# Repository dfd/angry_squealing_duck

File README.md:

# Angry Squealing Duck

A guitar pedal: a thick octave-fuzz feeding a dynamics-driven envelope band-pass
("Q-Tron") filter. Designed and voiced entirely in **ngspice**, validated against
real-part models, ready for KiCad.

**Controls (4 knobs + 2 footswitches):**
- **Volume** — output level
- **Anger** — fuzz amount / sustain (Big-Muff-style)
- **Squeal** — up-octave level: CCW = none, ~noon = "ring on top", CW = octave-dominant blast
- **Quack** — envelope band-pass intensity (ganged sweep depth + resonance Q)
- **Master** true-bypass footswitch, and a dedicated **Squeal (octave) footswitch**
  (kick the octave in/out, Hoof-Reaper style)

All knobs CCW = that effect off.

## Signal architecture

```
 IN ─► Input buffer ─► SPLIT ─┬─ AUDIO: Fuzz(Anger) ─┬─► BP envelope filter(Quack) ──┐
                              │                       └─► Octave-up(Squeal) ─► fixed HP┤─►[Volume]─► OUT
                              └─ CONTROL: Envelope follower (raw) ─► Iabc (cutoff) ─────┘
```

Key voicing decisions (each one earned the hard way — see `git log` / memory):
- **Octave AFTER the fuzz** (Octavia / Fender-Blender pattern): rectifying the distorted
  signal yields a prominent ring. Octave *before* the fuzz buried it ~30 dB under the
  fuzz's odd harmonics.
- **Body and octave on separate filter paths** ("hybrid" route): the fuzz body goes
  through the **band-pass** envelope filter (it quacks); the octave goes through a
  **fixed high-pass** (stays clear/bright instead of being swept under). A single shared
  filter ("mixed") muffled the octave.
- **Envelope tapped from the RAW split** (pre-fuzz) so the filter tracks picking dynamics
  — fuzz compresses dynamics away.

## Design choices

- Single **9 V** supply, **op-amp-buffered 4.5 V** virtual ground (`vref`) — a passive
  divider sags under the high-gain fuzz. Every stage input is AC-coupled.
- **Fuzz** = 3-stage cascaded **Big-Muff-style soft-clipper** with asymmetric stages for
  warmth (`fuzz_muff.cir`, default). A single-stage hard clipper (`fuzz.cir`, DOD-250
  family) is kept selectable via the `muff` param.
- **Octave** = op-amp **precision full-wave rectifier** (`fwr.cir`), no transformer.
  `octave_gen.cir` produces octave-only; Squeal level is **quadratic** so noon = ring,
  full = blast (`goct=8`, ~+9 dB octave-over-body, calibrated on real DI clips).
- **Envelope follower** = precision rectifier + **2-pole averaging** (not peak-detect,
  which hunted in a ~12 Hz limit cycle that re-triggered the filter on held notes).
- **Filter** = **LM13700 OTA state-variable** filter (`vcf.cir` behavioral / `vcf_real.cir`
  real). Has LP/BP/HP/mixed taps (Q-Tron-style mode); the hybrid route uses BP for the
  body. Quack maps to a **linear Q (0.7→3.5)** and an envelope-swept cutoff (gm = Iabc).
  gm control is ground-referenced to avoid a virtual-ground latch.
- **Behavioral-ideal first** to lock topology/voicing, then **real part models** for build
  accuracy (`opamp_real.sub` = TL072, `lm13700.sub` = OTA) — validated: voicing essentially
  unchanged on real silicon. See `memory` / `real-parts-and-build-notes`.

## Status

Design, voicing, real-part validation, **and a routed KiCad PCB are complete.**

| done | |
|---|---|
| ✅ | All blocks designed + integrated (input buffer → fuzz → octave → filter → volume) |
| ✅ | Voiced by ear on real guitar (MOTU M2), grid of Squeal×Anger×Quack rendered |
| ✅ | Real part models (TL072 + LM13700) — chain converges, voicing holds |
| ✅ | All-real buildable netlist (`pedal_build.cir`, no B-sources) — re-validated |
| ✅ | Quack sweep restored: V-to-I gain ×73 → body cutoff ~280 Hz→2.1 kHz, auditioned-good |
| ✅ | KiCad PCB: placed, auto-routed, gerbers exported |
| ✅ | **Tier-1 de-risk audit** (`kicad/AUDIT.md`): caught + fixed **10 reversed diodes**; added per-IC decoupling + Schottky protection + center-neg polarity; **DRC 0 unconnected / 0 violations** |

**Quack note:** the real envelope is tiny (~0.04 V peak), so the V-to-I needs high gain
(`Rdi`/`Rdj` = 1.5k, `Rdf`/`Rdk` = 110k → ×73) for the filter to sweep. Quack is most
audible at lower Squeal — at full Squeal the octave sits on top by design.

**Audit caught a board-killer:** `duck.py` (hand-translated) had 10/14 diodes reversed
(fuzz clippers + both rectifiers) — ERC + sim pass anyway since the SPICE is a separate,
correct source. Fixed to match SPICE; see `kicad/AUDIT.md`. **Not yet hardware-validated:**
real noise floor + the LM13700 filter's behavior (the `/50` attenuation hack, Iabc ceiling) —
confirm by breadboarding the filter + fuzz before fab (`kicad/breadboard/`).

## Layout

- `spice/lib/`    — models: `opamp.sub` (ideal), `opamp_real.sub` (TL072),
  `lm13700.sub` (OTA), `diode.mod` (1N4148), `supply.cir` (buffered vref)
- `spice/blocks/` — one `.subckt` per block: `input_buffer`, `fuzz`, `fuzz_muff`, `fwr`,
  `octave_rect`/`octave_gen`, `hpf`, `gmint`+`vcf`/`vcf_real`, `envfollow`,
  `duck`(mixed)/`duck_split`(hybrid/parallel), `pedal`
- `spice/tests/`  — per-block test benches
- `sim/`          — Python harness: `run.py`, `render.py`, `octave_balance.py`,
  `fft_report.py`, `spicelib.py`, `extract_sample.py`
- `audio/in/`     — committed DI samples; `audio/out/` — rendered WAVs (git-ignored)
- `raw_wavs/`     — large source recordings (git-ignored)
- `kicad/`        — the board, generated programmatically:
  - `duck.py` (SKiDL netlist generator) → `duck.net` (ERC-clean) + `BOM.md`
  - `build_pcb.py` (pcbnew: parse netlist → place → board) ; `finish_pcb.py` (values + GND pour)
  - `duck.kicad_pcb` (routed, DRC-clean) ; `gerbers/` + `duck.drl` + `duck-pos.csv` (fab-ready)
  - `duck_3d_top.png` / `duck_3d_persp.png` (3D renders; or open the `.kicad_pcb` in pcbnew → `Alt+3`)
  - `AUDIT.md` (netlist-translation audit + gap fixes) ; `BOM.md` ; `COST.md` (build-cost estimate)
  - `pedal_build.cir` in `spice/blocks/` is the all-real buildable schematic-of-record
- `kicad/breadboard/` — prototype-first docs (build it on a breadboard before the PCB):
  - `BUILD_GUIDE.md` (staged bring-up) + `CONNECTIONS.md` (per-stage wiring tables, net = row)
  - `gen_blocks.py` / `make_tables.py` (generators) ; `0*.png` drawn schematics (simple stages)
- `audio/out/build_grid/` + `build_grid_orig/` — full real-parts grids (Squeal×Anger×Quack ∈ {0,0.5,1})

## KiCad / PCB workflow

The board is generated entirely by script (no GUI), bridging two Pythons because
`pcbnew` is built for system Python 3.14 while the sim harness uses uv's 3.13:
```
# 1. netlist (uv / 3.13)
KICAD8_SYMBOL_DIR=/usr/share/kicad/symbols uv run kicad/duck.py     # -> duck.net (+ ERC)
# 2. place + board (system python 3.14, needs pcbnew)
/usr/bin/python3 kicad/build_pcb.py                                 # -> duck.kicad_pcb
# 3. route: export DSN, run freerouting (needs a display, e.g. :0), import SES
/usr/bin/python3 -c "import pcbnew,sys; b=pcbnew.LoadBoard('kicad/duck.kicad_pcb'); pcbnew.ExportSpecctraDSN(b,'/tmp/duck.dsn')"
DISPLAY=:0 java -jar freerouting.jar -de /tmp/duck.dsn -do /tmp/duck.ses -mp 14
/usr/bin/python3 -c "import pcbnew; b=pcbnew.LoadBoard('kicad/duck.kicad_pcb'); pcbnew.ImportSpecctraSES(b,'/tmp/duck.ses'); pcbnew.SaveBoard('kicad/duck.kicad_pcb',b)"
# 4. finishing pass (snap values + GND pour) + checks + fab outputs
/usr/bin/python3 kicad/finish_pcb.py
kicad-cli pcb drc kicad/duck.kicad_pcb
kicad-cli pcb export gerbers --output kicad/gerbers/ kicad/duck.kicad_pcb
```
Board: 2-layer, 175×120 mm (1590DD-class), 6× TL074 + 1× LM13700 + 14× 1N4148,
4 knobs (Volume / Anger / Squeal / Quack-dual-gang). No graphical schematic
(eeschema has no scripting API) — `pedal_build.cir` + `duck.py` are the design-of-record.

## Prototype it first (breadboard)

`kicad/breadboard/` holds **prototype-first** docs. Build + test the circuit on solderless
breadboards one stage at a time before committing to the PCB — see `BUILD_GUIDE.md` for the
staged bring-up order (supply → input → fuzz → octave → envelope → V-to-I → filter → output)
and `CONNECTIONS.md` for per-stage wiring tables (**each net = one breadboard row**; IC pins
annotated). Each stage uses its own op-amp IC (not the PCB's shared packing) so it tests
standalone. Regenerate with `gen_blocks.py` + `make_tables.py`. (SKiDL's schematic auto-router
only handles the simple stages, so the dense ones are table-only — better for breadboarding anyway.)

## Workflow

Run a block test bench:
```
uv run sim/run.py spice/tests/tb_input_buffer.cir
```
Render guitar through the pedal (→ `audio/out/`):
```
# the LOCKED, buildable design (= the PCB): real parts, no B-sources, V-to-I gain x73
uv run sim/render.py [wav] --build --squeal 1 --anger 0.8 --quack 0.6 [--subdir name]
# the behavioral routes (faster iteration / experiments):
uv run sim/render.py [wav] --route hybrid --squeal 1 --anger 0.8 --quack 0.6 [--real]
```
- **`--build`** = `pedal_build.cir`, the all-real buildable pedal that matches the PCB (use this).
- `--real` = TL072 + LM13700 models on the behavioral chain · `--route` = mixed|hybrid|parallel
- Scratch files are unique per render, so render a grid in parallel on many cores:
  `... | xargs -P 24 -I A sh -c 'uv run sim/render.py A'`
  (the committed `audio/out/build_grid/` + `build_grid_orig/` are the `--build` grids of
  Squeal×Anger×Quack ∈ {0, 0.5, 1.0} on both DI samples).

Measure octave-vs-body level on real clips (don't trust single-note benches — they
over-read the octave ~6 dB):
```
uv run sim/octave_balance.py --wav audio/in/di_sample.wav --squeal 1.0 --goct 8
```

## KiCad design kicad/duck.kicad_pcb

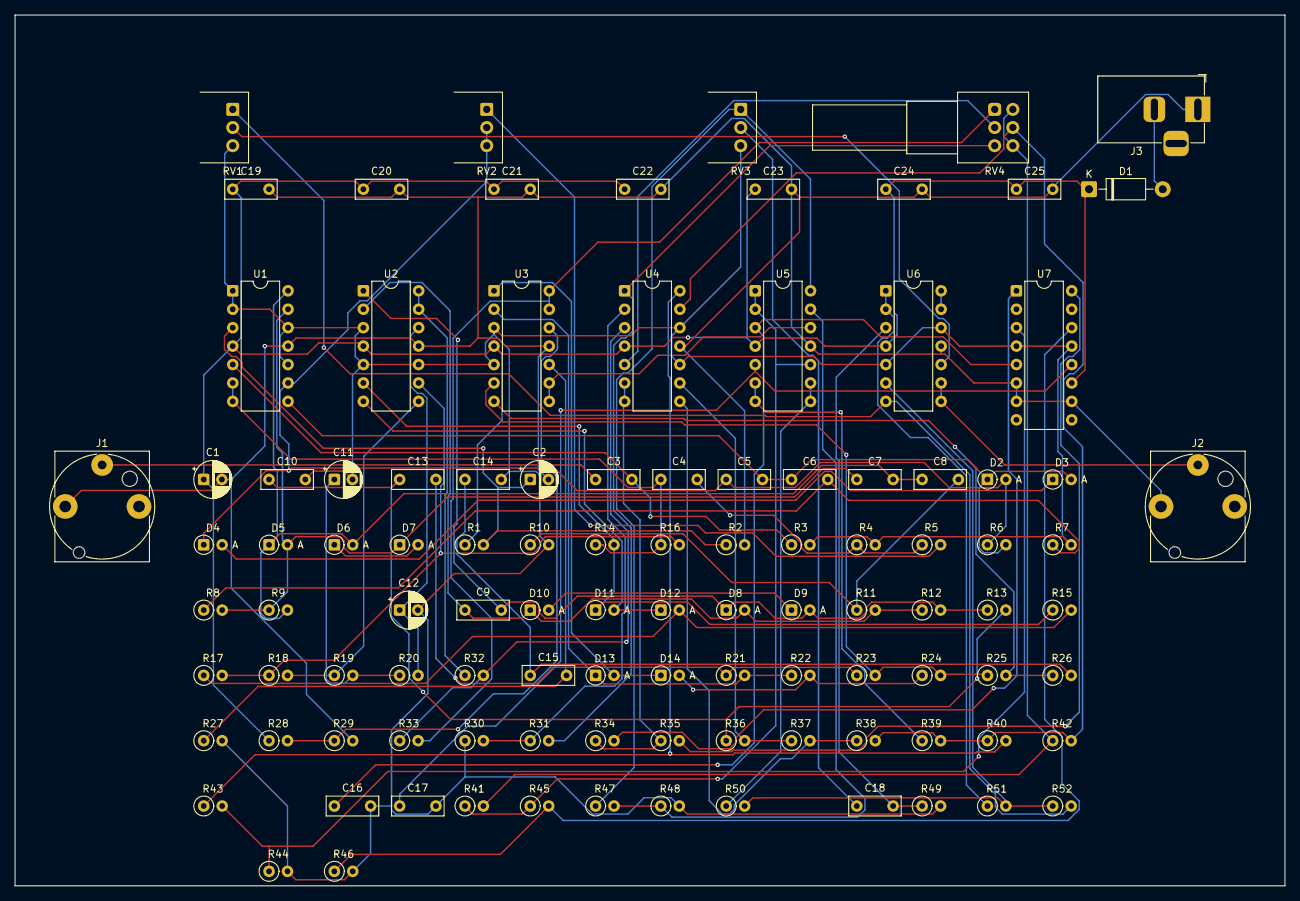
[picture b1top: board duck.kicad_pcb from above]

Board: 2 copper layers, 175.0 x 120.0 mm, 105 parts (0 on the bottom side), 70 nets.

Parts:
C1: 100u; CP_Radial_D5.0mm_P2.50mm
C2: 47u; CP_Radial_D5.0mm_P2.50mm
C3, C4, C6, C8, C19, C20, C21, C22, C23, C24, C25: 100n; C_Rect_L7.0mm_W2.5mm_P5.00mm
C5, C7, C9: 1.5n; C_Rect_L7.0mm_W2.5mm_P5.00mm
C10: 27n; C_Rect_L7.0mm_W2.5mm_P5.00mm
C11, C12: 220n; CP_Radial_D5.0mm_P2.50mm
C13: 47n; C_Rect_L7.0mm_W2.5mm_P5.00mm
C14: 12n; C_Rect_L7.0mm_W2.5mm_P5.00mm
C15: 1u; C_Rect_L7.0mm_W2.5mm_P5.00mm
C16, C17: 10n; C_Rect_L7.0mm_W2.5mm_P5.00mm
C18: 22n; C_Rect_L7.0mm_W2.5mm_P5.00mm
D1: 1N5817; D_DO-41_SOD81_P10.16mm_Horizontal
D2, D3, D4, D5, D6, D7, D8, D9, D10, D11, D12, D13, D14: 1N4148; D_DO-35_SOD27_P2.54mm_Vertical_AnodeUp
J1, J2: AudioJack2; Jack_6.35mm_Neutrik_NJ3FD-V_Vertical
J3: Barrel_Jack; BarrelJack_Horizontal
R1, R2, R6, R9, R27, R28: 100k; R_Axial_DIN0207_L6.3mm_D2.5mm_P2.54mm_Vertical
R3, R4, R7, R10: 1M; R_Axial_DIN0207_L6.3mm_D2.5mm_P2.54mm_Vertical
R5, R13: 2.2k; R_Axial_DIN0207_L6.3mm_D2.5mm_P2.54mm_Vertical
R8, R11: 12k; R_Axial_DIN0207_L6.3mm_D2.5mm_P2.54mm_Vertical
R12, R47: 68k; R_Axial_DIN0207_L6.3mm_D2.5mm_P2.54mm_Vertical
R14, R15, R16, R18, R21, R22, R23, R25, R34, R35, R36, R37, R38, R39, R40, R48: 10k; R_Axial_DIN0207_L6.3mm_D2.5mm_P2.54mm_Vertical
R17, R24: 4.7k; R_Axial_DIN0207_L6.3mm_D2.5mm_P2.54mm_Vertical
R19, R20: 15k; R_Axial_DIN0207_L6.3mm_D2.5mm_P2.54mm_Vertical
R26: 3.3k; R_Axial_DIN0207_L6.3mm_D2.5mm_P2.54mm_Vertical
R29, R49, R50, R51, R52: 22k; R_Axial_DIN0207_L6.3mm_D2.5mm_P2.54mm_Vertical
R30, R32: 1.5k; R_Axial_DIN0207_L6.3mm_D2.5mm_P2.54mm_Vertical
R31, R33: 110k; R_Axial_DIN0207_L6.3mm_D2.5mm_P2.54mm_Vertical
R41: 6.8k; R_Axial_DIN0207_L6.3mm_D2.5mm_P2.54mm_Vertical
R42: 39k; R_Axial_DIN0207_L6.3mm_D2.5mm_P2.54mm_Vertical
R43, R45: 47k; R_Axial_DIN0207_L6.3mm_D2.5mm_P2.54mm_Vertical
R44, R46: 1k; R_Axial_DIN0207_L6.3mm_D2.5mm_P2.54mm_Vertical
RV1, RV2, RV3: 100k; Potentiometer_Alps_RK097_Single_Horizontal
RV4: 100k; Potentiometer_Alps_RK097_Dual_Horizontal
U1, U2, U3, U4, U5, U6: TL074; DIP-14_W7.62mm
U7: LM13700; DIP-16_W7.62mm

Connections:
BODYF: R50.1, U5.8, U5.9
BP: R41.1, R45.1, U5.1, U5.2, U5.10
CV: R32.1, U2.13, U2.14
ECTL: R31.2, RV4.3, U4.1
FZ: C10.1, C13.1, R13.2, R36.1
FZ1: C5.2, C6.1, D2.1, D3.2, R6.2, U1.8
FZ2: C7.2, C8.1, D5.1, D6.2, R9.2, U1.14
FZ3: C9.2, D8.1, D9.2, R12.2, R13.1, U2.1
GND: C1.2, C2.2, C19.2, C20.2, C21.2, C22.2, C23.2, C24.2, C25.2, J1.S, J2.S, J3.1, R2.2, R29.2, U1.11, U2.11, U3.11, U4.11, U5.11, U6.11, U7.6, U7.7, U7.10
HP: R40.2, R43.1, U4.14
LP: R39.1, U5.6, U5.7
unnamed: C4.2, R4.1, R5.1
unnamed: R5.2, RV2.1
unnamed: C5.1, D2.2, D4.1, R6.1, RV2.2, RV2.3, U1.9
unnamed: D3.1, D4.2
unnamed: C6.2, R7.1, R8.1
unnamed: C7.1, D5.2, D7.1, R8.2, R9.1, U1.13
unnamed: D6.1, D7.2
unnamed: C8.2, R10.1, R11.1
unnamed: C9.1, D8.2, D10.1, R11.2, R12.1, U2.2
unnamed: D9.1, D10.2
unnamed: D11.1, R14.2, R15.1, U2.6
unnamed: R16.2, R17.2, R18.1, U2.9
unnamed: D12.2, R15.2, R17.1
unnamed: D11.2, D12.1, U2.7
unnamed: C11.1, R19.2, R20.1
unnamed: C12.1, R20.2, U2.12
unnamed: C13.2, R21.1, R23.1
unnamed: R25.2, R26.1, U3.7
unnamed: D13.1, R21.2, R22.1, U3.2
unnamed: R23.2, R24.2, R25.1, U3.6
unnamed: D14.2, R22.2, R24.1
unnamed: D13.2, D14.1, U3.1
unnamed: C14.1, C15.1, R26.2
unnamed: C15.2, R27.1, U3.10
unnamed: R28.2, R29.1, U3.12
unnamed: R30.2, R31.1, U4.2
unnamed: R32.2, R33.1, U4.3
unnamed: R34.2, U7.1
unnamed: R35.2, U7.16
unnamed: R37.2, R38.1, U4.8
unnamed: R36.2, R37.1, U4.9
unnamed: R38.2, R39.2, R40.1, R42.2, RV4.5, U4.13
unnamed: R41.2, R42.1, RV4.4, RV4.6
unnamed: R43.2, R44.1, U7.3
unnamed: C16.1, U5.3, U7.5
unnamed: R45.2, R46.1, U7.14
unnamed: C17.1, U5.5, U7.12
unnamed: R47.1, RV3.1, U5.14
unnamed: R47.2, R48.1, U5.13
unnamed: C18.1, RV3.2
unnamed: C18.2, R49.1, U6.3
unnamed: R50.2, R51.2, R52.1, U6.6
unnamed: RV1.2, U6.10
unnamed: U6.13, U6.14
NP: C3.2, R3.1, U1.5
NREF: C2.1, R1.2, R2.1, U1.3
OCTF: R51.1, U6.1, U6.2
OCTV: U3.8, U3.9, U5.12
OPRE: R52.2, RV1.1, U6.7
OUT: J2.T, U6.8, U6.9
RABS_E: R18.2, R19.1, U2.8
SIG: C4.1, R14.1, R16.1, U1.6, U1.7
SIN: C3.1, J1.T
VBIAS: R34.1, R35.1, U4.6, U4.7
VBP: RV4.2, U4.5
VCC: C1.1, C19.1, C20.1, C21.1, C22.1, C23.1, C24.1, C25.1, D1.1, R1.1, R28.1, U1.4, U2.4, U3.4, U4.4, U5.4, U6.4, U7.11
VOFF: R33.2, RV4.1, U3.13, U3.14
VRAW: D1.2, J3.2
VREF: C10.2, C11.2, C12.2, C14.2, C16.2, C17.2, R3.2, R4.2, R7.2, R10.2, R27.2, R30.1, R44.2, R46.2, R48.2, R49.2, RV1.3, RV3.3, U1.1, U1.2, U1.10, U1.12, U2.3, U2.5, U2.10, U3.3, U3.5, U4.10, U4.12, U6.5, U6.12, U7.4, U7.13

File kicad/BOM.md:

# Angry Squealing Duck - BOM (from kicad/duck.net)

## ICs (7)
- 6x TL074: U1, U2, U3, U4, U5, U6
- 1x LM13700: U7

## Potentiometers (4)
- 4x 100k: RV1, RV2, RV3, RV4

## Diodes (14)
- 13x 1N4148: D2, D3, D4, D5, D6, D7, D8, D9, D10, D11, D12, D13, D14
- 1x 1N5817: D1

## Resistors (52)
- 16x 10k: R14, R15, R16, R18, R21, R22, R23, R25, R34, R35, R36, R37, R38, R39, R40, R48
- 6x 100k: R1, R2, R6, R9, R27, R28
- 5x 22k: R29, R49, R50, R51, R52
- 4x 1M: R3, R4, R7, R10
- 2x 12k: R8, R11
- 2x 68k: R12, R47
- 2x 2.2k: R5, R13
- 2x 4.7k: R17, R24
- 2x 15k: R19, R20
- 2x 1.5k: R30, R32
- 2x 110k: R31, R33
- 2x 47k: R43, R45
- 2x 1k: R44, R46
- 1x 3.3k: R26
- 1x 6.8k: R41
- 1x 39k: R42

## Capacitors (25)
- 11x 100n: C3, C4, C6, C8, C19, C20, C21, C22, C23, C24, C25
- 3x 1.5n: C5, C7, C9
- 2x 220n: C11, C12
- 2x 10n: C16, C17
- 1x 100u: C1
- 1x 27n: C10
- 1x 47n: C13
- 1x 12n: C14
- 1x 1u: C15
- 1x 22n: C18
- 1x 47u: C2

## Connectors (3)
- 2x AudioJack2: J1, J2
- 1x Barrel_Jack: J3

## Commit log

2026-06-25 second attempt at pedal circuit
2026-06-25 updated opamp
2026-06-25 pushed effects further, added muff fuzz
2026-06-25 turned up octave and fuzz more
2026-06-25 made HP/BP/LP and mixed (0.7 HP, 0.7 BP). HP and mixed bring out the octave more
2026-06-25 big muff, hybrid octave, rescaled quack sound good.
2026-06-25 final sound, and real parts demo matches
2026-06-25 updated README.
2026-06-26 validated SPICE design. buildable all-real design. Some voicing drift on quack.
2026-06-26 kicad pcb design is done
2026-06-26 improved quack sweep with real parts
2026-06-26 board updated with improved quack
2026-06-26 added breadboard instructions
2026-06-26 adding estimated costs
2026-06-26 audited and correct pcb design, updated breadboard instructions
